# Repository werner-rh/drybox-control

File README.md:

DryBox dryController
===

## Version 0.50 ESP 01

## Requirements
- Arduino IDE 1.8.2 or higher
- NewliquidCrystal (I2C) https://github.com/fmalpartida/New-LiquidCrystal/tree/master
- ESP8266: PubSubClient by Nick O'Leary
- SEP8266: ArduinoJson by Benoit Blanchon

- 3D printing files and other parts list: https://www.printables.com/de/model/724722-filament-dry-box-heated-ventilated-arduino-control
- Improved version: https://www.printables.com/model/1093573-enhanced-filament-dry-box-heated-ventilated-arduin

## Description
Controller for an active heated and ventilated Filament DryBox. The Dryer contains a PTC Heater and a Fan for fresh dry air.

Original version is for Arduino Nano
Improved Version is for Wemos D1 Mini (ESP8266); additional features:
- sensor data transmission via mqtt
- example files for mqtt --> telegraf --> influxdb --> grafana
- PCB layout in kicad
- ==> pay attention to set your wifi credentials in Secrets.h (for ESP8266)

With one Heater, the box may barely reaches 55 degree. As max i reached 57 degree. I recommend not to go over 52-53 degree. If you need higher temperatures, install a second heater. The MosFet switch will manage this. But you also need a stronger power supply (12V, 8-10A). A simple improvement is insulating the walls inside. I used a car sun protect shield, with reflection and insulating. This improves the performance of the box sigifignant. The warm up is much faster and also eaysier to to reach 55 degrees.

## Recommended drying temperatures
- PLA, PLA+                : 40-45 degree
- ABS, ABS+,  PETG         : 45-50 degree
- PVA,PVB, ASA, TPU, PMMA  : 50-55 degree

## Trouble shooting for ESP8266 version
- Check step by step in the chain  esp --> mqtt --> telegraf --> influxdb --> grafana
- Let DryBox run for all of the following tests.
- esp: Check the serial console: Is wifi working? Do you have a mqtt connection? Have you changed the corresponding parameters in Secrets.h?
- mqtt: Use the commandline or the tool mqtt explorer to observe the mqtt messages from DryBox. There should be a main node labeled like in Secrets.h
- telegraf: telegraf has input and output interfaces. First check the log for any errors in the input interface. Then check if the output interface wrote into the file listed in telegraf.conf. If this is working, you can comment out the file section in telegraf.conf. Now check telegraf´s output interface to influxdb. Do you have set the influxdb token in telegraf.conf?
- influxdb: Have you generated a bucket "DryBox" an configured this in Secrets.h? Have you generated a token connected to the bucket for telegraf and grafana with the necessary permissions? Use the influxdb data explorer to check if any DryBox data is written from telegraf.
- grafana: Have you created a datasource "InfluxDB" with query language "flux"? Is the organization (e.g. "Homelab") the same in the config files for telegraf, influxdb and grafana? Did you use the right token from influxdb? Did you select the configured datasource when importing the grafana.json file?

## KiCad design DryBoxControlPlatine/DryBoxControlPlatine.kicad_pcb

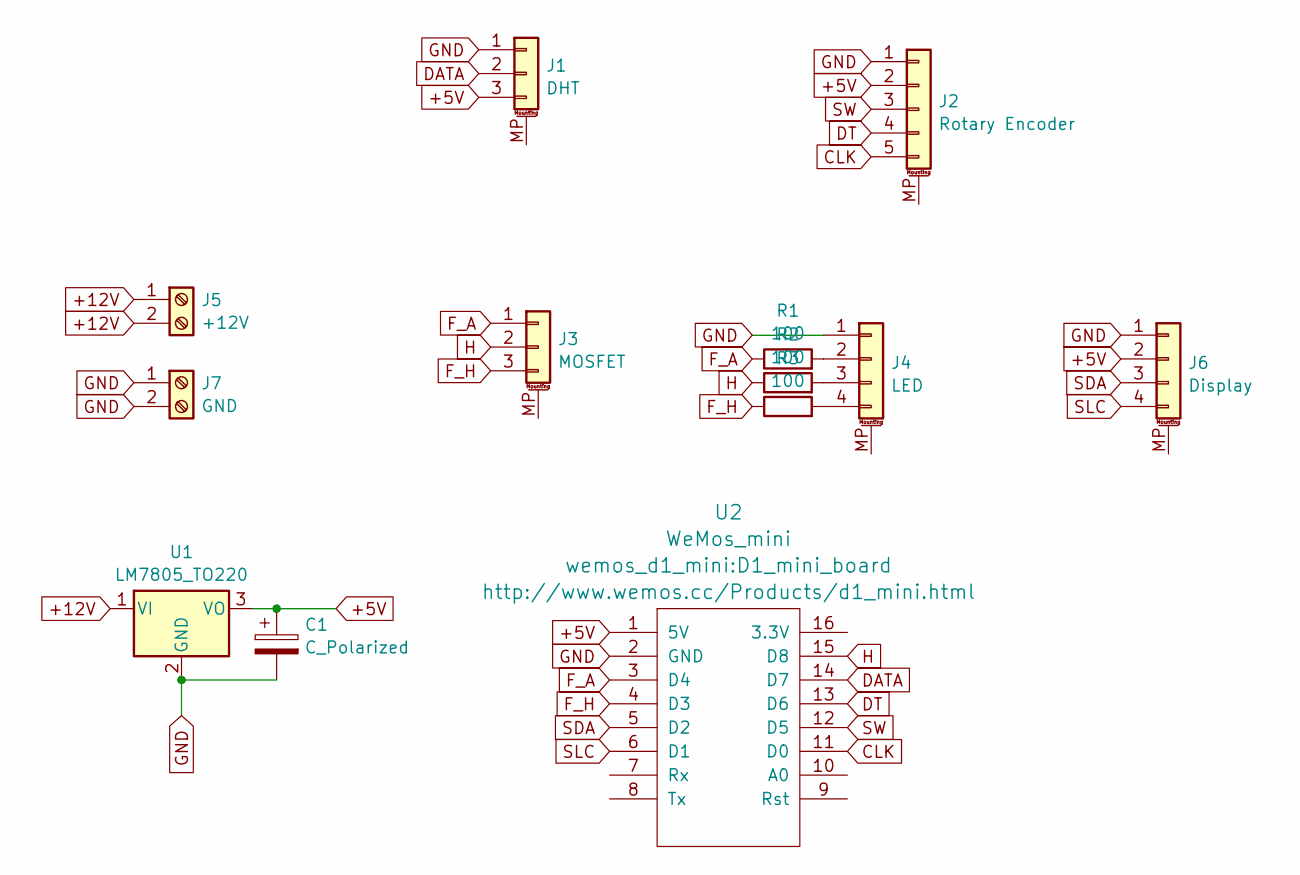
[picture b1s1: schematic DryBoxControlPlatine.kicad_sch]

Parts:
C1: C_Polarized; CP_Radial_D5.0mm_P2.50mm
J1: DHT; PinHeader_1x03_P2.54mm_Vertical
J2: Rotary Encoder; PinHeader_1x05_P2.54mm_Vertical
J3: MOSFET; PinHeader_1x03_P2.54mm_Vertical
J4: LED; PinHeader_1x04_P2.54mm_Vertical
J5: +12V; TerminalBlock_Phoenix_MKDS-1,5-2-5.08_1x02_P5.08mm_Horizont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
J6: Display; PinHeader_1x04_P2.54mm_Vertical
J7: GND; TerminalBlock_Phoenix_MKDS-1,5-2-5.08_1x02_P5.08mm_Horizont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
R1, R2, R3: 100; R_Axial_DIN0204_L3.6mm_D1.6mm_P2.54mm_Vertical
U1: LM7805_TO220; TO-220-3_Vertical
U2: WeMos_mini; D1_mini_board

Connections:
+5V: C1.1, J1.3, J2.2, J6.2, U1.3 (VO), U2.1 (5V)
+12V: J5.1, J5.2, U1.1 (VI)
CLK: J2.5, U2.11 (D0)
DATA: J1.2, U2.14 (D7)
DT: J2.4, U2.13 (D6)
F_A: J3.1, R1.1, U2.3 (D4)
F_H: J3.3, R3.1, U2.4 (D3)
GND: C1.2, J1.1, J2.1, J4.1, J6.1, J7.1, J7.2, U1.2 (GND), U2.2 (GND)
H: J3.2, R2.1, U2.15 (D8)
unnamed: J4.2, R1.2
unnamed: J4.3, R2.2
unnamed: J4.4, R3.2
SDA: J6.3, U2.5 (D2)
SLC: J6.4, U2.6 (D1)
SW: J2.3, U2.12 (D5)

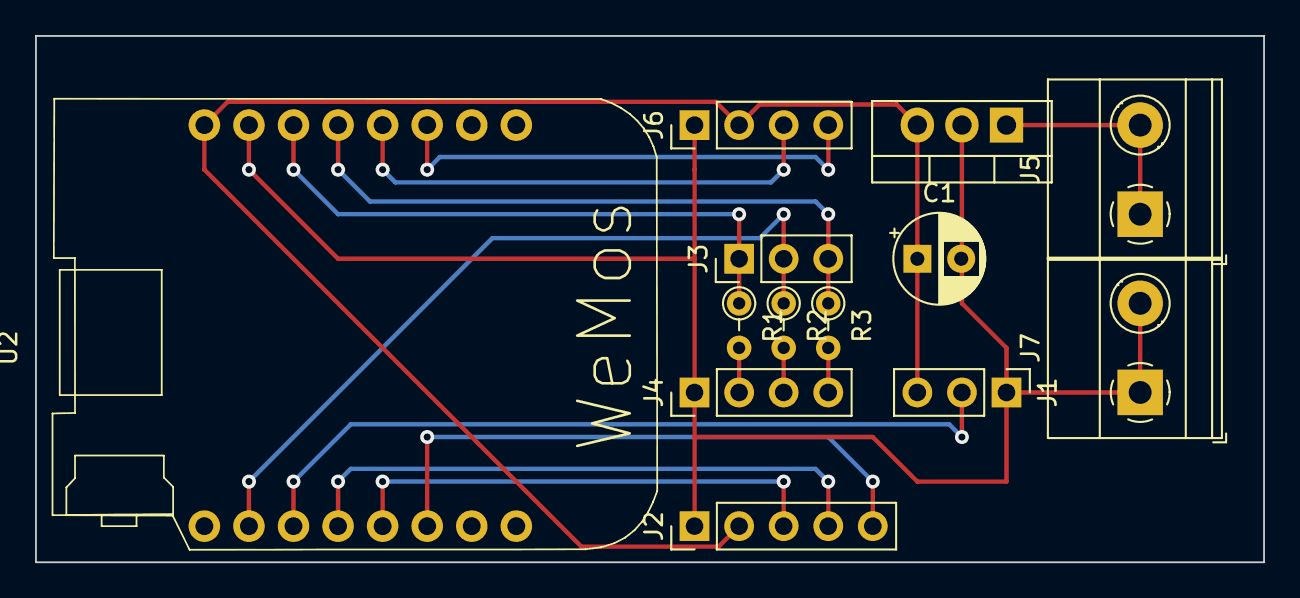
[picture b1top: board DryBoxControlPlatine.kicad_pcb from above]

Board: 2 copper layers, 70.0 x 30.0 mm, 13 parts (0 on the bottom side), 15 nets.

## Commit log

2024-01-14 Rename DryBoxControl.ZIP to DryBoxControl-v046.ZIP
    version 0.46
2024-03-30 Add files via upload
    added the files unziped
2024-03-30 Delete DryBoxControl-v046.ZIP
    added the files unziped. No need for the zipfile anymore
2024-05-08 Add files via upload
    changed some comments
2024-05-08 Add files via upload
    adjust comments and a further fix in dryController
2024-05-09 Add files via upload
    refactored heating data and implemented turbo mode
2024-05-11 Add files via upload
    added adjustable values for ventilation time and final ventilation time
2024-05-14 Add files via upload
    added value airExchangeIntervallMinutes
2024-06-10 Update DryBoxControl.ino
    handle sensor error
2024-06-10 Update DryBoxDisplay.cpp
    add screen error message
2024-06-11 Update DryBoxControl.ino
    clean up
2024-06-18 Update DryBoxControl.h
    version bump
2024-06-19 Update README.md
    adjust version in readme.md to sensor error handling
2024-06-25 Update DryBoxControl.ino
    Fan rpm readout
2024-06-25 Update DryBoxControl.ino
    bug fix in Read fan tachometer
2024-06-29 Update DryBoxControl.ino
    minor bug fixes
2024-06-30 1.0 update
2024-07-01 Update DryBoxControl.ino
    small change for rolling message logick
2024-08-04 Add files via upload
    roll back to 0.48 because the fan tacho changes and extension causes compiler error due to uncomplete code
2024-08-07 Add files via upload
    set main properly to 0.49
2024-10-14 Replaced DHT11 with SHT31
2024-10-20 Ported to Wemos D1 mini (ESP8266); changed to software timer interrupt; added wifi and mqtt; corrected misspelling of pwm
2024-11-11 Added counter for dht nan-signal
2024-11-11 Changed dht counter to 3
2024-11-11 migrated mqtt messages to JSON format
2024-12-01 PCB (Kicad) for Wemos D1 Mini added
2024-12-01 Added ESP8266 README
2024-12-01 Added telgraf and grafana config
2024-12-02 changed version number to 0.50 added notable changes to changelog
2024-12-02 changed Version to 0.50
2024-12-03 Add files via upload
    fix missing setup for rotary encoder switch
2024-12-04 Corrected misspelling of PWM
2024-12-04 Fixed wrong ESP8266-exclusion of paragraph display error; merged from 0.49.1 issue "Encoder Button not configured" https://github.com/werner-rh/drybox-control/issues/16
2024-12-04 added hint for wifi credentials
2024-12-04 added robustness for wifi and mqtt connection; drybox works even without connections
2025-03-15 Update grafana.json: Used generic export with generic InfluxDB-ID for better import on different system
2025-03-16 Update README.md
    Added trouble shooting for ESP version
2025-03-16 Update README.md
    File naming correction in section "grafana"
2025-03-21 Update README.md
    Version number
2025-03-21 Update CHANGELOG.md
    Versioning
